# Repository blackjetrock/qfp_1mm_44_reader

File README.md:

# qfp_1mm_44_reader
Reader PCB for 1mm ptich 44p pin qfp

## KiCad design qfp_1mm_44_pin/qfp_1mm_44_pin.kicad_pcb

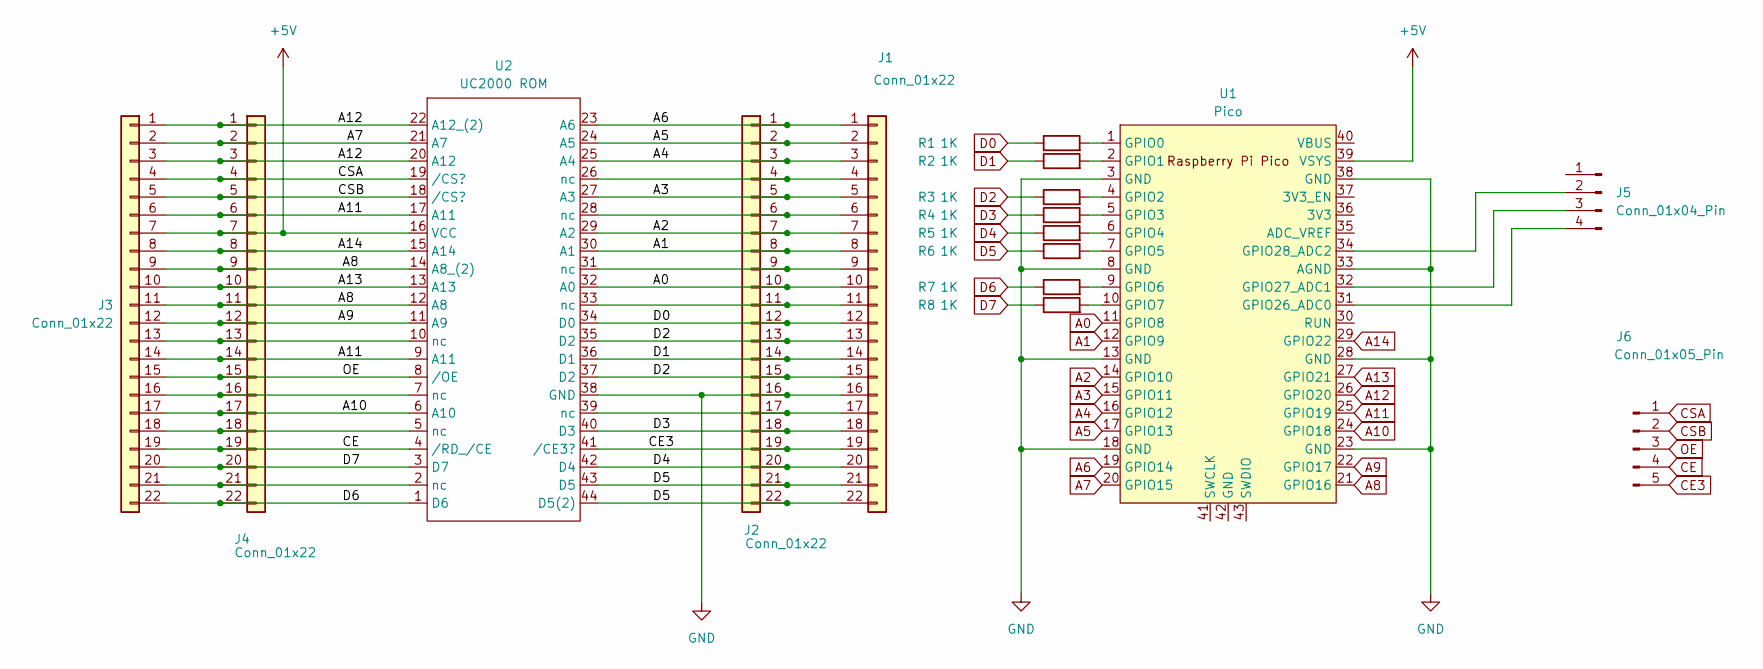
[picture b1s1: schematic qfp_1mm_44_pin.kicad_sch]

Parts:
J1, J2, J3, J4: Conn_01x22; PinHeader_1x22_P2.54mm_Vertical
J5: Conn_01x04_Pin; PinHeader_1x04_P2.54mm_Vertical
J6: Conn_01x05_Pin; PinHeader_1x05_P2.54mm_Vertical
R1, R2, R3, R4, R5, R6, R7, R8: 1K; R_0805_2012Metric_Pad1.20x1.40mm_HandSolder
U1: Pico; RPi_Pico_SMD_TH
U2: UC2000 ROM; qfp-44-1_0_pitch

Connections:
+5V: J3.7, J4.7, U1.39 (VSYS), U2.16 (VCC)
A0: J1.10, J2.10, U1.11 (GPIO8), U2.32 (A0)
A1: J1.8, J2.8, U1.12 (GPIO9), U2.30 (A1)
A2: J1.7, J2.7, U1.14 (GPIO10), U2.29 (A2)
A3: J1.5, J2.5, U1.15 (GPIO11), U2.27 (A3)
A4: J1.3, J2.3, U1.16 (GPIO12), U2.25 (A4)
A5: J1.2, J2.2, U1.17 (GPIO13), U2.24 (A5)
A6: J1.1, J2.1, U1.19 (GPIO14), U2.23 (A6)
A7: J3.2, J4.2, U1.20 (GPIO15), U2.21 (A7)
A8: J3.9, J3.11, J4.9, J4.11, U1.21 (GPIO16), U2.12 (A8), U2.14 (A8_(2))
A9: J3.12, J4.12, U1.22 (GPIO17), U2.11 (A9)
A10: J3.17, J4.17, U1.24 (GPIO18), U2.6 (A10)
A11: J3.6, J3.14, J4.6, J4.14, U1.25 (GPIO19), U2.9 (A11), U2.17 (A11)
A12: J3.1, J3.3, J4.1, J4.3, U1.26 (GPIO20), U2.20 (A12), U2.22 (A12_(2))
A13: J3.10, J4.10, U1.27 (GPIO21), U2.13 (A13)
A14: J3.8, J4.8, U1.29 (GPIO22), U2.15 (A14)
CE: J3.19, J4.19, J6.4, U2.4 (/RD_/CE)
CE3: J1.19, J2.19, J6.5, U2.41 (/CE3?)
CSA: J3.4, J4.4, J6.1, U2.19 (/CS?)
CSB: J3.5, J4.5, J6.2, U2.18 (/CS?)
D0: J1.12, J2.12, R1.1, U2.34 (D0)
D1: J1.14, J2.14, R2.1, U2.36 (D1)
D2: J1.13, J1.15, J2.13, J2.15, R3.1, U2.35 (D2), U2.37 (D2)
D3: J1.18, J2.18, R4.1, U2.40 (D3)
D4: J1.20, J2.20, R5.1, U2.42 (D4)
D5: J1.21, J1.22, J2.21, J2.22, R6.1, U2.43 (D5), U2.44 (D5(2))
D6: J3.22, J4.22, R7.1, U2.1 (D6)
D7: J3.20, J4.20, R8.1, U2.3 (D7)
GND: J1.16, J2.16, U1.3 (GND), U1.8 (GND), U1.13 (GND), U1.18 (GND), U1.23 (GND), U1.28 (GND), U1.33 (AGND), U1.38 (GND), U2.38 (GND)
unnamed: J1.4, J2.4, U2.26 (nc)
unnamed: J1.6, J2.6, U2.28 (nc)
unnamed: J1.9, J2.9, U2.31 (nc)
unnamed: J1.11, J2.11, U2.33 (nc)
unnamed: J1.17, J2.17, U2.39 (nc)
unnamed: J3.13, J4.13, U2.10 (nc)
unnamed: J3.16, J4.16, U2.7 (nc)
unnamed: J3.18, J4.18, U2.5 (nc)
unnamed: J3.21, J4.21, U2.2 (nc)
unnamed: J5.2, U1.34 (GPIO28_ADC2)
unnamed: J5.3, U1.32 (GPIO27_ADC1)
unnamed: J5.4, U1.31 (GPIO26_ADC0)
unnamed: R1.2, U1.1 (GPIO0)
unnamed: R2.2, U1.2 (GPIO1)
unnamed: R3.2, U1.4 (GPIO2)
unnamed: R4.2, U1.5 (GPIO3)
unnamed: R5.2, U1.6 (GPIO4)
unnamed: R6.2, U1.7 (GPIO5)
unnamed: R7.2, U1.9 (GPIO6)
unnamed: R8.2, U1.10 (GPIO7)
OE: J3.15, J4.15, J6.3, U2.8 (/OE)

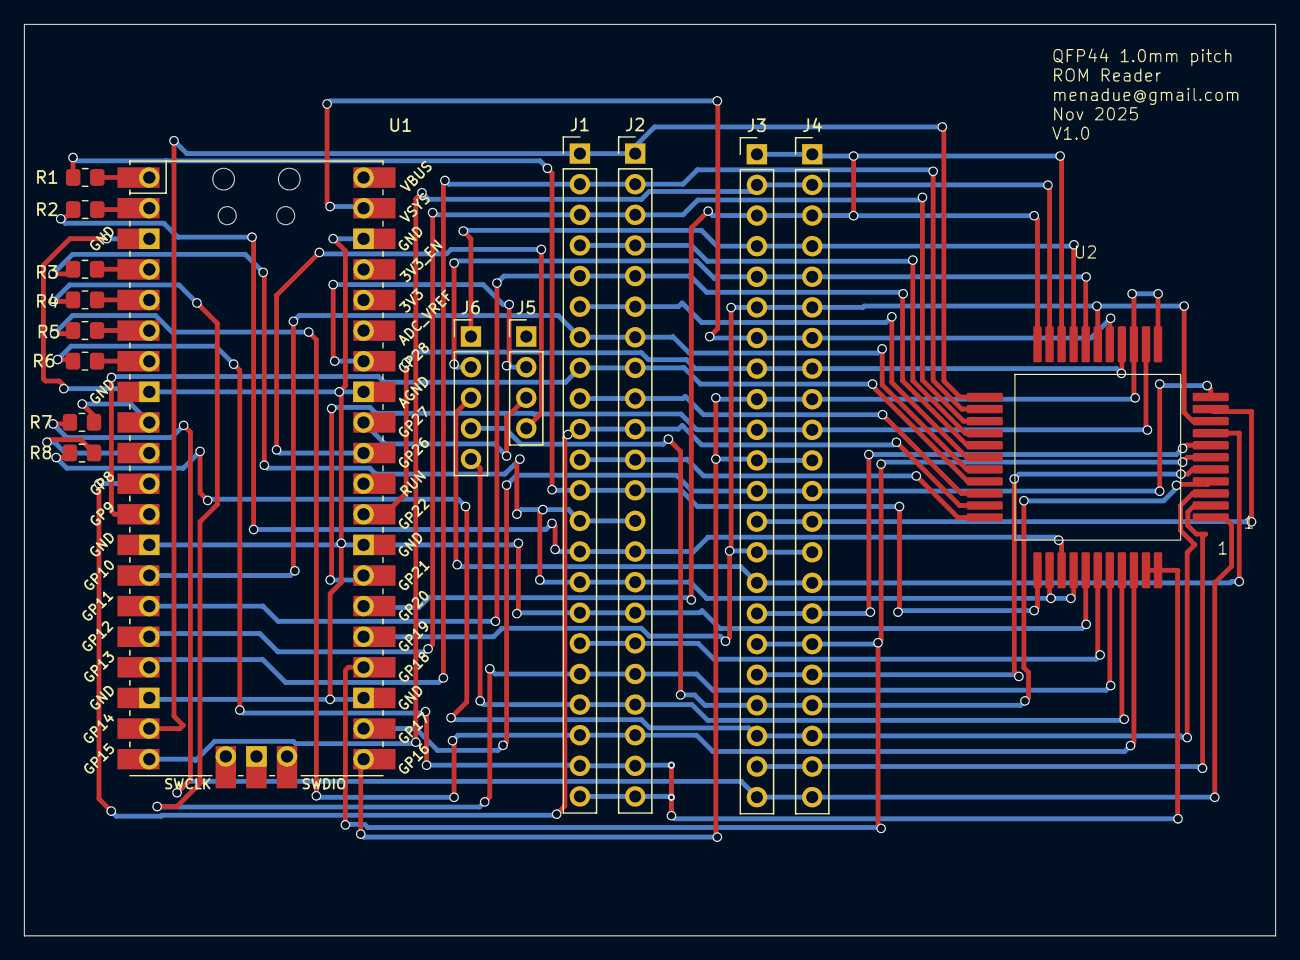
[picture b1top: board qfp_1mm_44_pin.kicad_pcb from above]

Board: 2 copper layers, 103.8 x 75.6 mm, 16 parts (0 on the bottom side), 50 nets.

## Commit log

2025-12-09 "Update"
